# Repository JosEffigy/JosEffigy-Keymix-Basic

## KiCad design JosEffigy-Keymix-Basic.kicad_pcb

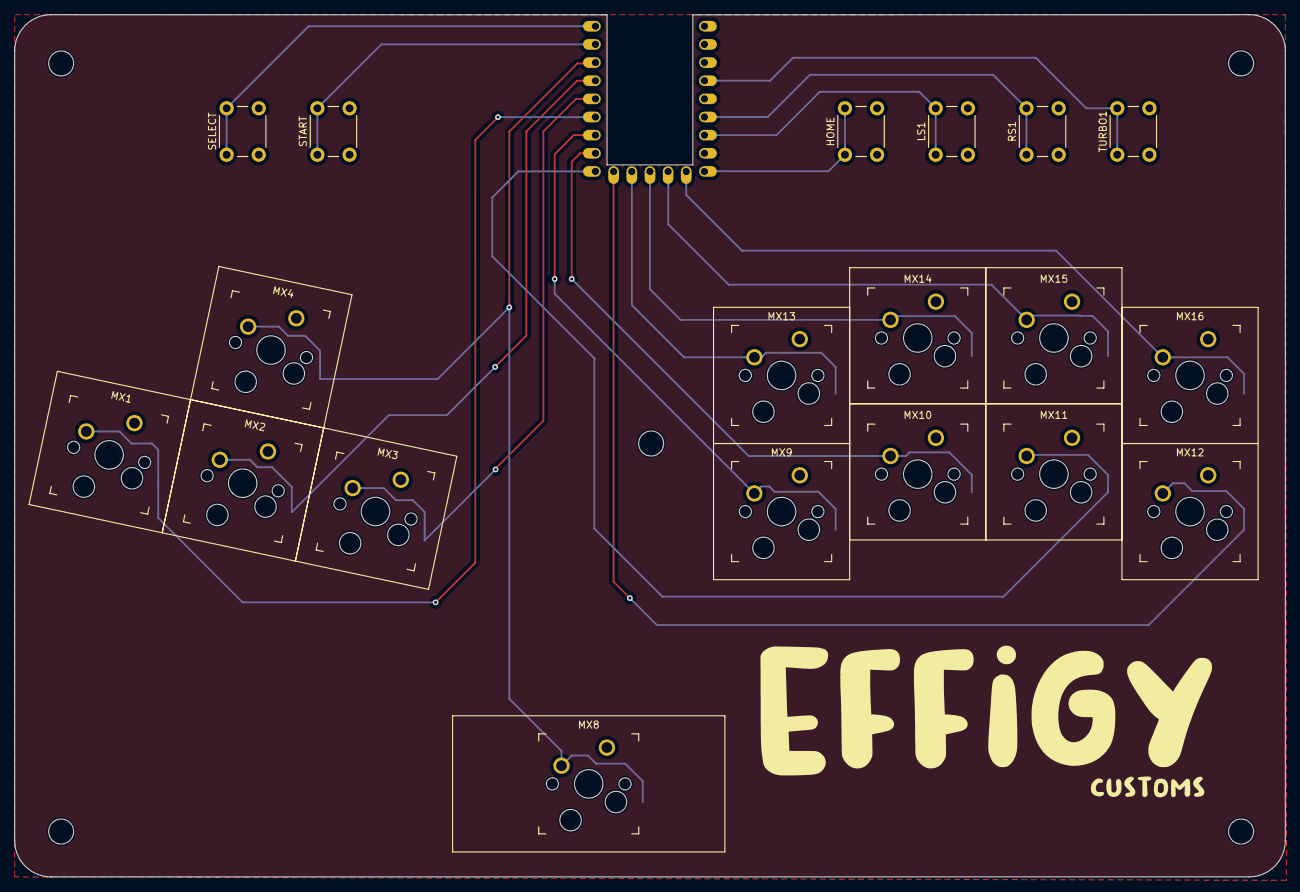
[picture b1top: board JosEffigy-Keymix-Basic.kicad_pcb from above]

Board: 2 copper layers, 177.8 x 120.6 mm, 25 parts (1 on the bottom side), 19 nets.

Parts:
HOME: MX-NoLED; SW_PUSH_6mm_H5mm
LS1: MX-NoLED; SW_PUSH_6mm_H5mm
MX1, MX2, MX3, MX4, MX8, MX9, MX10, MX11, MX12, MX13, MX14, MX15, MX16: MX-NoLED; Kailh_socket_MX_optional
RS1: MX-NoLED; SW_PUSH_6mm_H5mm
SELECT: MX-NoLED; SW_PUSH_6mm_H5mm
START: MX-NoLED; SW_PUSH_6mm_H5mm
TURBO1: MX-NoLED; SW_PUSH_6mm_H5mm
U1: Pico; rp2040-zero-tht
h1, h1#2, h2, h3, h4: MountingHole_3.5mm

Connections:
1K: MX9.2 (ROW), U1.7 (6)
1P: MX13.2 (ROW), U1.11 (10)
2K: MX10.2 (ROW), U1.8 (7)
2P: MX14.2 (ROW), U1.12 (11)
3K: MX11.2 (ROW), U1.9 (8)
3P: MX15.2 (ROW), U1.13 (12)
4K: MX12.2 (ROW), U1.10 (9)
4P: MX16.2 (ROW), U1.14 (13)
DOWN: MX2.2 (ROW), U1.4 (3)
GND: HOME.2, LS1.2, MX1.1 (COL), MX2.1 (COL), MX3.1 (COL), MX4.1 (COL), MX8.1 (COL), MX9.1 (COL), MX10.1 (COL), MX11.1 (COL), MX12.1 (COL), MX13.1 (COL), MX14.1 (COL), MX15.1 (COL), MX16.1 (COL), RS1.2, SELECT.2, START.2, TURBO1.2, U1.22 (GND)
HOME: HOME.1, U1.15 (14)
LEFT: MX1.2 (ROW), U1.6 (5)
LS: LS1.1, U1.17 (26)
RIGHT: MX3.2 (ROW), U1.5 (4)
RS: RS1.1, U1.18 (27)
SELECT: SELECT.1, U1.1 (0)
START: START.1, U1.2 (1)
TURBO: TURBO1.1, U1.20 (29)
UP: MX4.2 (ROW), MX8.2 (ROW), U1.3 (2)

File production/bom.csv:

Designator,Footprint,Quantity,Value,LCSC Part #
"HOME, LS1, RS1, SELECT, START, TURBO1",SW_PUSH_6mm_H5mm,6,MX-NoLED,
"MX1, MX10, MX11, MX12, MX13, MX14, MX15, MX16, MX2, MX3, MX4, MX8, MX9",Kailh_socket_MX_optional,13,MX-NoLED,
U1,rp2040-zero-tht,1,Pico,

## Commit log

2023-06-18 1.2
    Added center mounting hole
